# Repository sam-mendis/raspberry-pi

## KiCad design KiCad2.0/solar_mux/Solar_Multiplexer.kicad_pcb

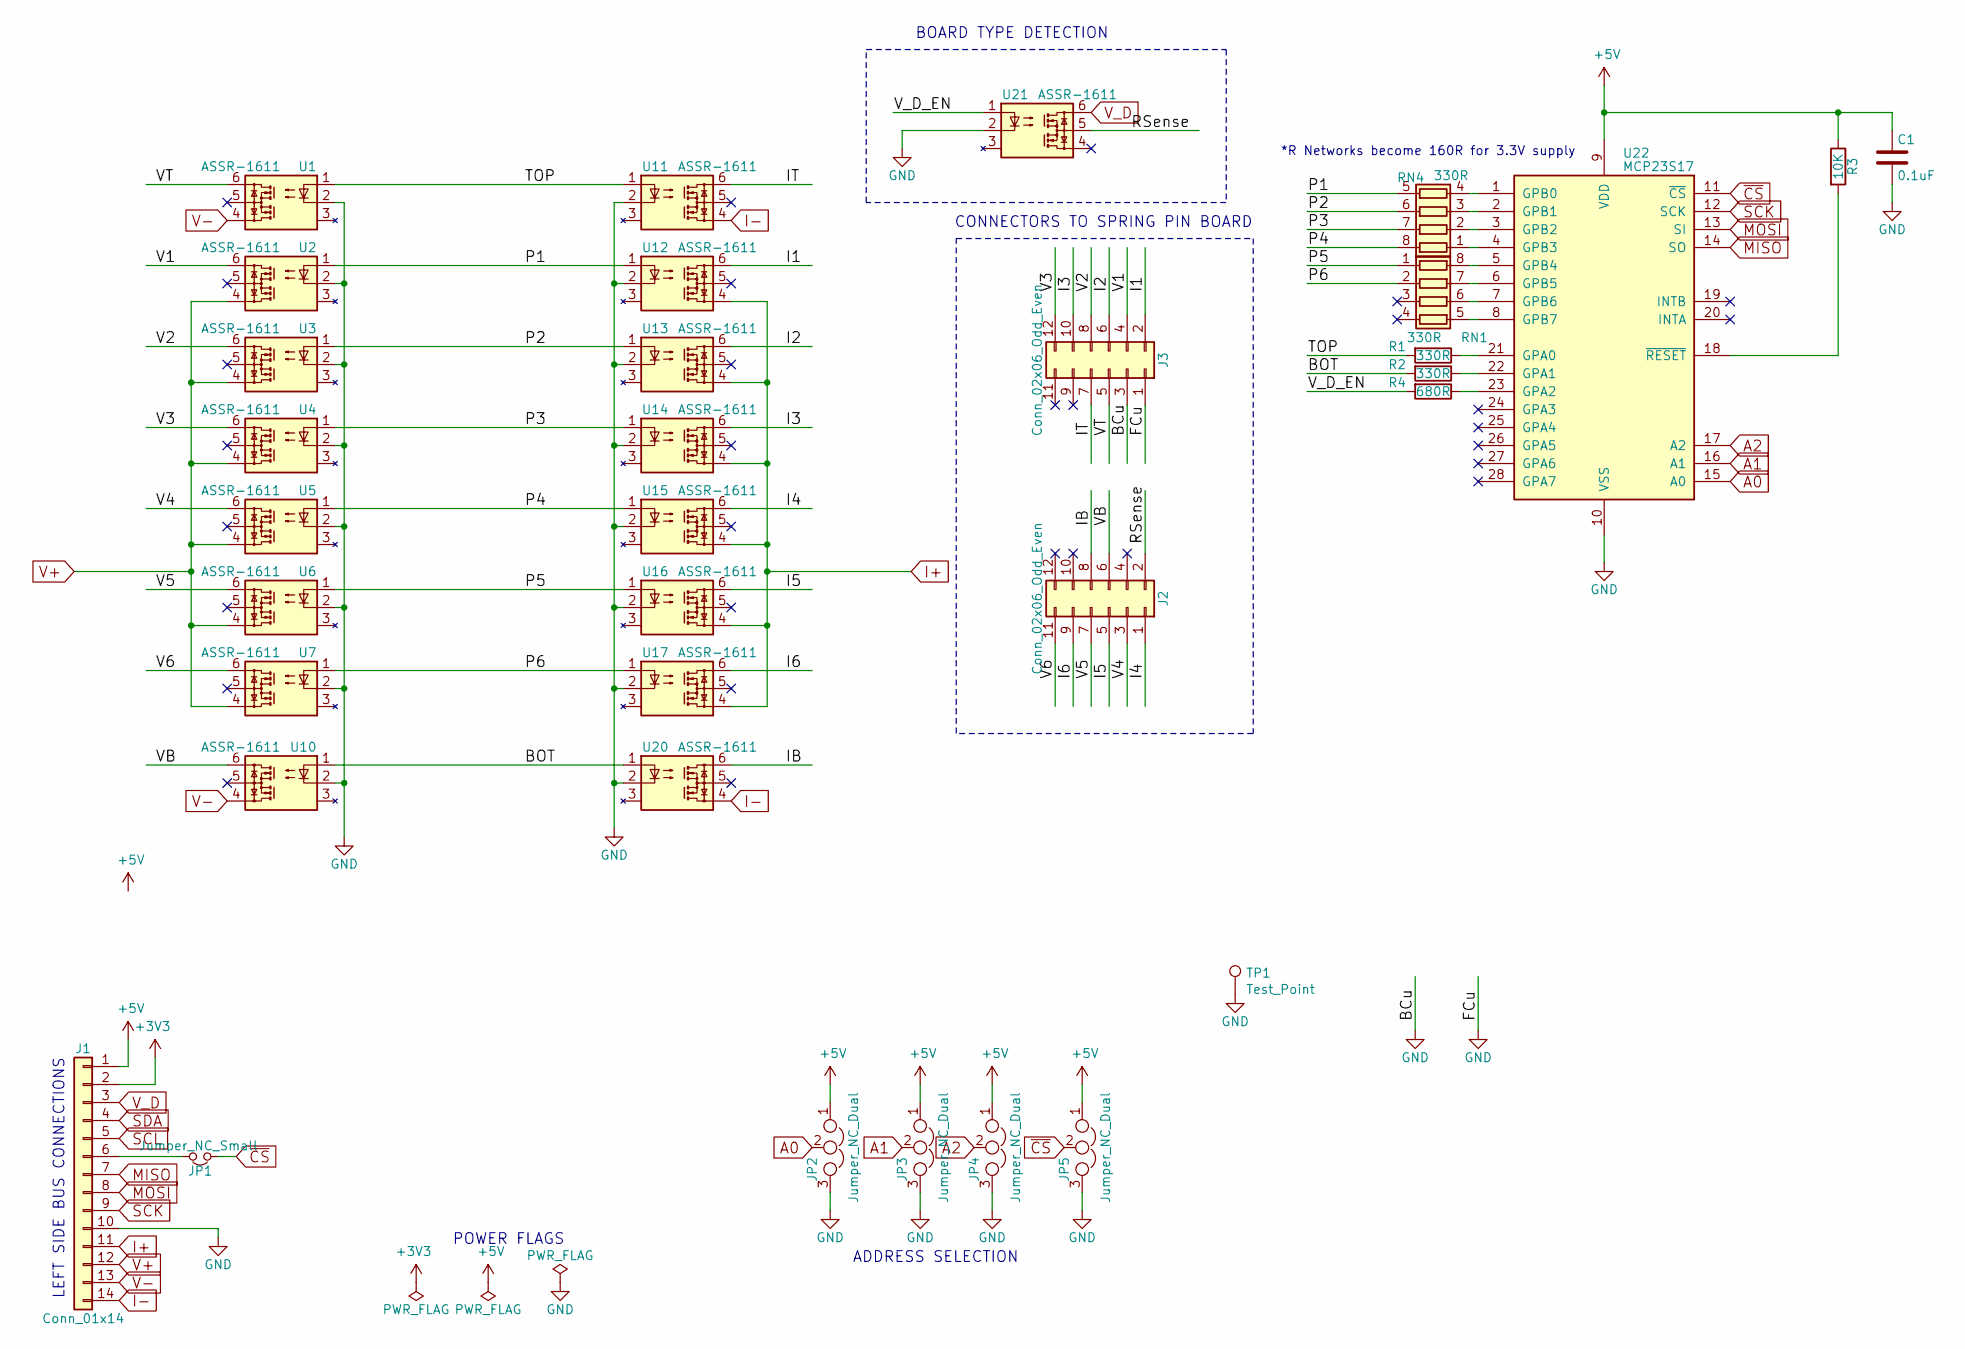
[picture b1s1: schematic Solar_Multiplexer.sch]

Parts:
C1: 0.1uF; CP_Radial_D8.0mm_P2.50mm; farnellCode 1759312
J1: Conn_01x14; PinHeader_1x14_P2.54mm_Vertical; farnellCode 2037821
J2: Conn_02x06_Odd_Even; PinHeader_2x06_P2.54mm_Vertical
J3: Conn_02x06_Odd_Even; PinHeader_2x06_P2.54mm_Vertical; FarnellPart 1930232
JP1: Jumper_NC_Small; SolderJumper-2_P1.3mm_Open_RoundedPad1.0x1.5mm
JP2, JP3, JP4, JP5: Jumper_NC_Dual; SolderJumper-3_P1.3mm_Open_RoundedPad1.0x1.5mm_NumberLabels
R1, R2: 330R; R_Axial_DIN0309_L9.0mm_D3.2mm_P15.24mm_Horizontal; farnellCode 2073607
R3: 10K; R_Axial_DIN0309_L9.0mm_D3.2mm_P15.24mm_Horizontal; farnellCode 2826357
R4: 680R; R_Axial_DIN0309_L9.0mm_D3.2mm_P15.24mm_Horizontal; farnellCode 2694489
RN1, RN4: 330R; R_Array_Convex_4x1206; digikey 744C083331JPCT-ND
TP1: Test_Point; TestPoint_Pad_2.5x2.5mm; farnell code 2293786
U1, U2, U3, U4, U5, U6, U7, U10, U11, U12, U13, U14, U15, U16, U17, U20, U21: ASSR-1611; DIP-6_W7.62mm; farnellCode 1708441
U22: MCP23S17; DIP-28_W7.62mm; farnellCode 1292238

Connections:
+3V3: J1.2
+5V: C1.1, J1.1, JP2.1, JP3.1, JP4.1, JP5.1, R3.1, U22.9 (VDD)
/BOT: R2.2, U10.1, U20.1
/I1: J3.2, U12.6
/I2: J3.6, U13.6
/I3: J3.10, U14.6
/I4: J2.1, U15.6
/I5: J2.5, U16.6
/I6: J2.9, U17.6
/IB: J2.8, U20.6
/IT: J3.7, U11.6
/P1: RN4.5 (R4.2), U2.1, U12.1
/P2: RN4.6 (R3.2), U3.1, U13.1
/P3: RN4.7 (R2.2), U4.1, U14.1
/P4: RN4.8 (R1.2), U5.1, U15.1
/P5: RN1.1 (R1.1), U6.1, U16.1
/P6: RN1.2 (R2.1), U7.1, U17.1
/RSense: J2.2, U21.5
/TOP: R1.2, U1.1, U11.1
/V1: J3.4, U2.6
/V2: J3.8, U3.6
/V3: J3.12, U4.6
/V4: J2.3, U5.6
/V5: J2.7, U6.6
/V6: J2.11, U7.6
/VB: J2.6, U10.6
/VT: J3.5, U1.6
/V_D_EN: R4.2, U21.1
A0: JP2.2, U22.15 (A0)
A1: JP3.2, U22.16 (A1)
A2: JP4.2, U22.17 (A2)
GND: C1.2, J1.10, J3.1, J3.3, JP2.3, JP3.3, JP4.3, JP5.3, TP1.1, U1.2, U2.2, U3.2, U4.2, U5.2, U6.2, U7.2, U10.2, U11.2, U12.2, U13.2, U14.2, U15.2, U16.2, U17.2, U20.2, U21.2, U22.10 (VSS)
I+: J1.11, U12.4, U13.4, U14.4, U15.4, U16.4, U17.4
I-: J1.14, U11.4, U20.4
MISO: J1.7, U22.14 (SO)
MOSI: J1.8, U22.13 (SI)
unnamed: J1.6, JP1.2
unnamed: R1.1, U22.21 (GPA0)
unnamed: R2.1, U22.22 (GPA1)
unnamed: R3.2, U22.18 (~RESET~)
unnamed: R4.1, U22.23 (GPA2)
unnamed: RN1.5 (R4.2), U22.8 (GPB7)
unnamed: RN1.6 (R3.2), U22.7 (GPB6)
unnamed: RN1.7 (R2.2), U22.6 (GPB5)
unnamed: RN1.8 (R1.2), U22.5 (GPB4)
unnamed: RN4.1 (R1.1), U22.4 (GPB3)
unnamed: RN4.2 (R2.1), U22.3 (GPB2)
unnamed: RN4.3 (R3.1), U22.2 (GPB1)
unnamed: RN4.4 (R4.1), U22.1 (GPB0)
SCK: J1.9, U22.12 (SCK)
SCL: J1.5
SDA: J1.4
V+: J1.12, U2.4, U3.4, U4.4, U5.4, U6.4, U7.4
V-: J1.13, U1.4, U10.4
V_D: J1.3, U21.6
~CS: JP1.1, JP5.2, U22.11 (~CS~)

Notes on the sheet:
ADDRESS SELECTION
POWER FLAGS
BOARD TYPE DETECTION
CONNECTORS TO SPRING PIN BOARD
LEFT SIDE BUS CONNECTIONS
*R Networks become 160R for 3.3V supply

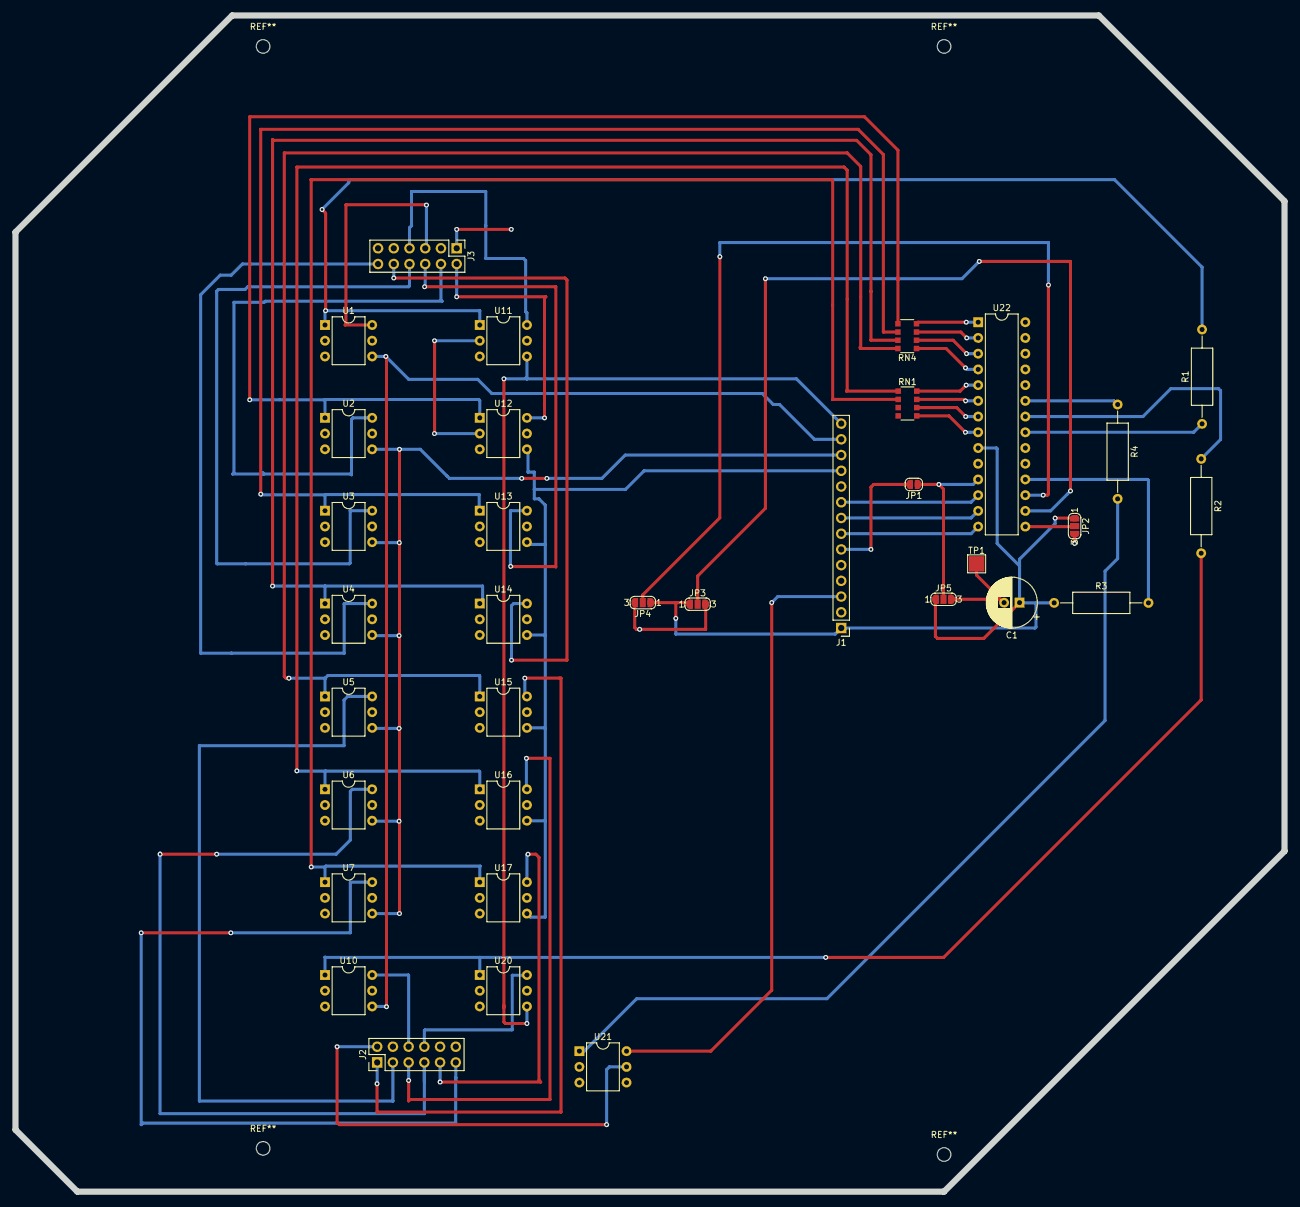
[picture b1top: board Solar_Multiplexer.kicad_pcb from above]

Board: 2 copper layers, 205.0 x 190.0 mm, 34 parts (0 on the bottom side), 53 nets.

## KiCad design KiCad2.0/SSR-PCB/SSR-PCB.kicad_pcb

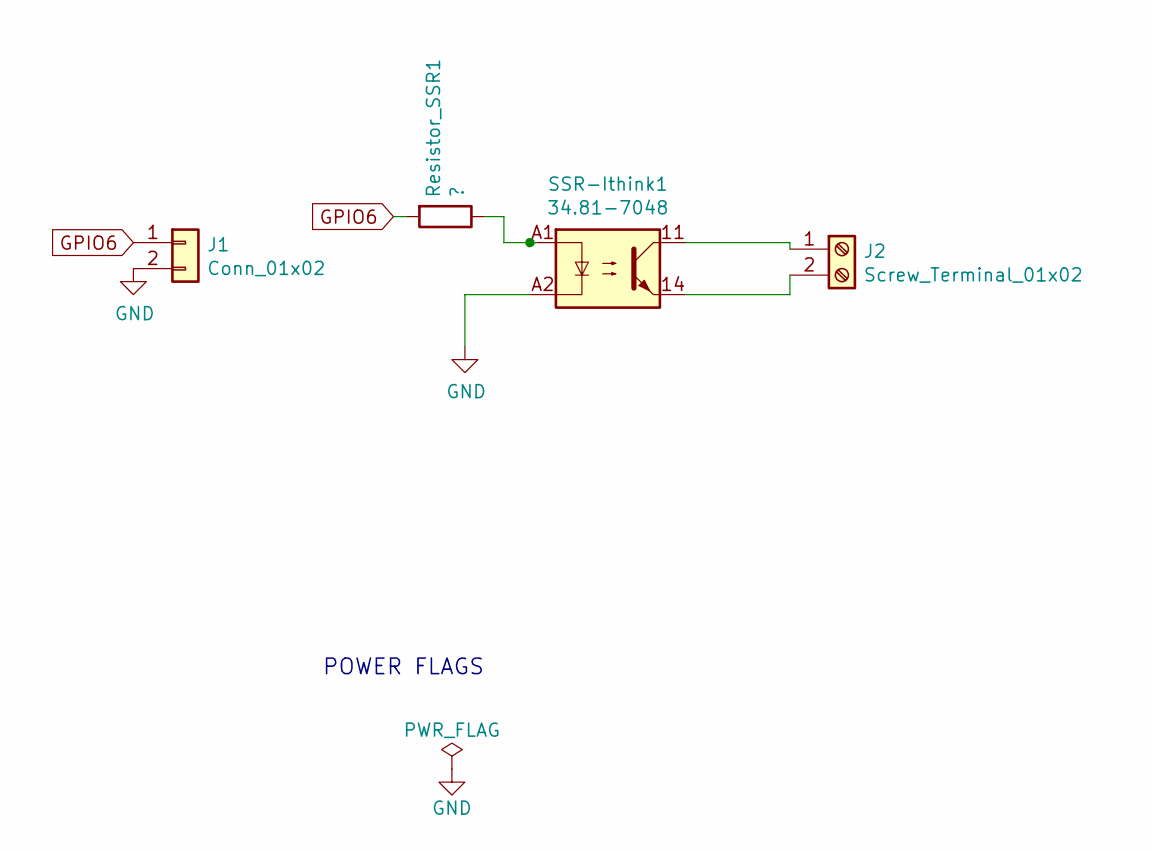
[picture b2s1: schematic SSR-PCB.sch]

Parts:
J1: Conn_01x02; PinHeader_1x02_P2.54mm_Vertical
J2: Screw_Terminal_01x02; TerminalBlock_Phoenix_MKDS-1,5-2_1x02_P5.00mm_Horizontal
Resistor_SSR1: ?; R_Axial_DIN0516_L15.5mm_D5.0mm_P20.32mm_Horizontal
SSR-Ithink1: 34.81-7048; Finder_34.81

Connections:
GND: J1.2, SSR-Ithink1.A2
GPIO6: J1.1, Resistor_SSR1.2
unnamed: J2.1, SSR-Ithink1.11
unnamed: J2.2, SSR-Ithink1.14
unnamed: Resistor_SSR1.1, SSR-Ithink1.A1

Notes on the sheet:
POWER FLAGS

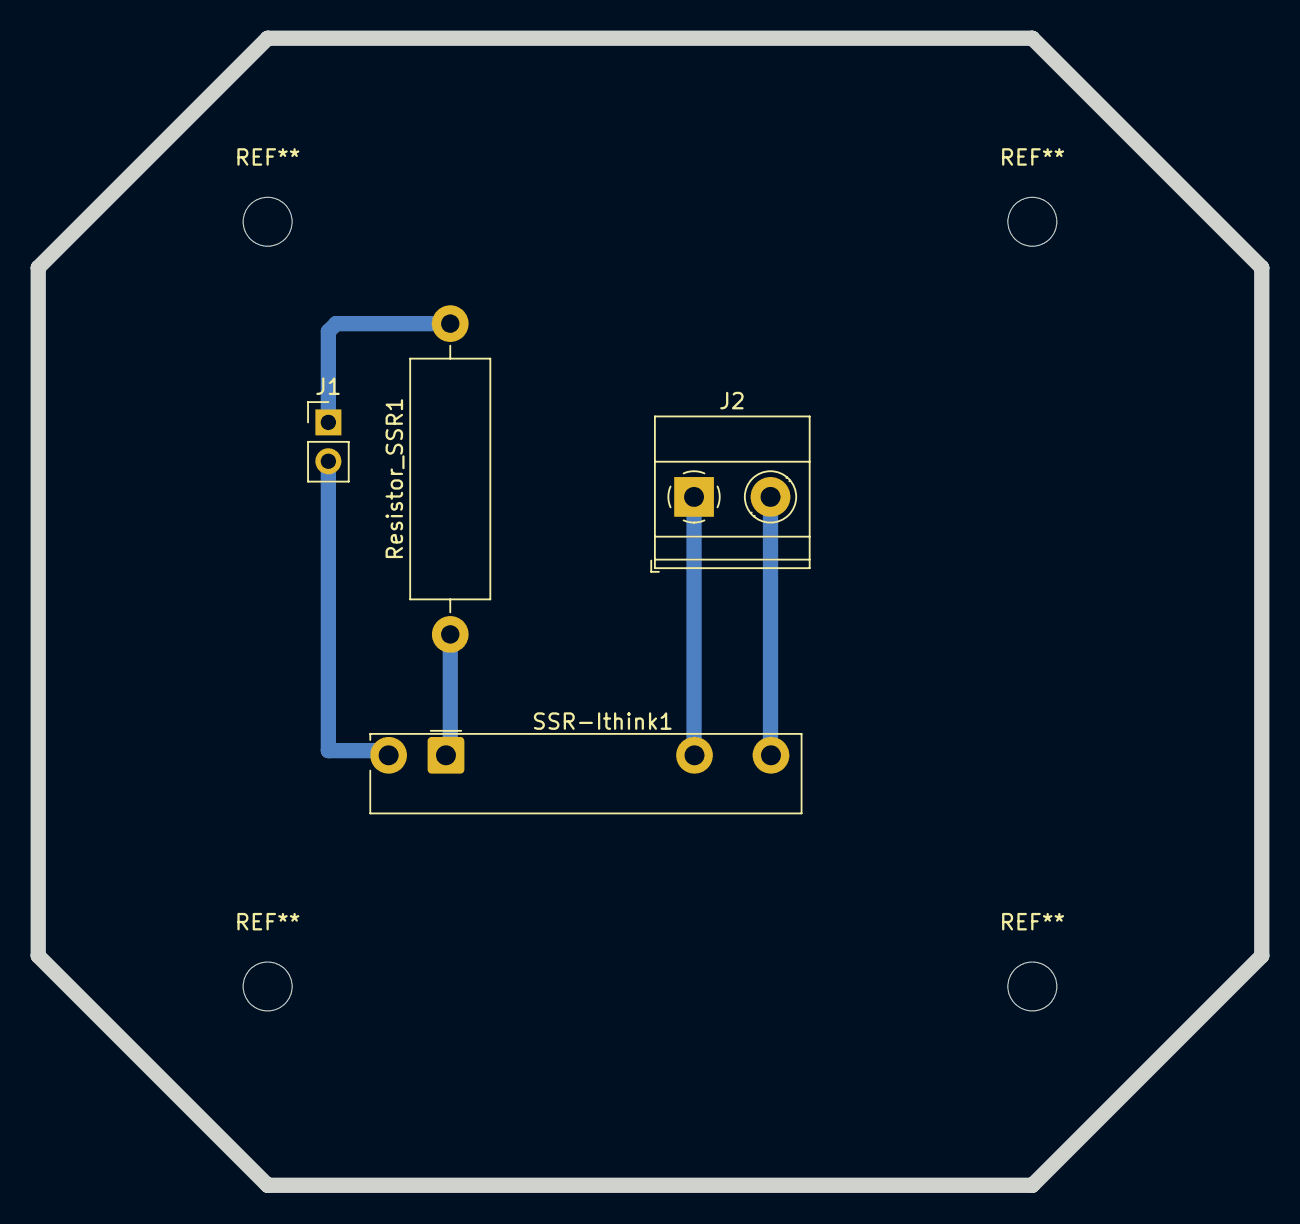
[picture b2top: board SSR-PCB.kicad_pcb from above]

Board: 4 copper layers, 80.0 x 75.0 mm, 4 parts (0 on the bottom side), 5 nets.

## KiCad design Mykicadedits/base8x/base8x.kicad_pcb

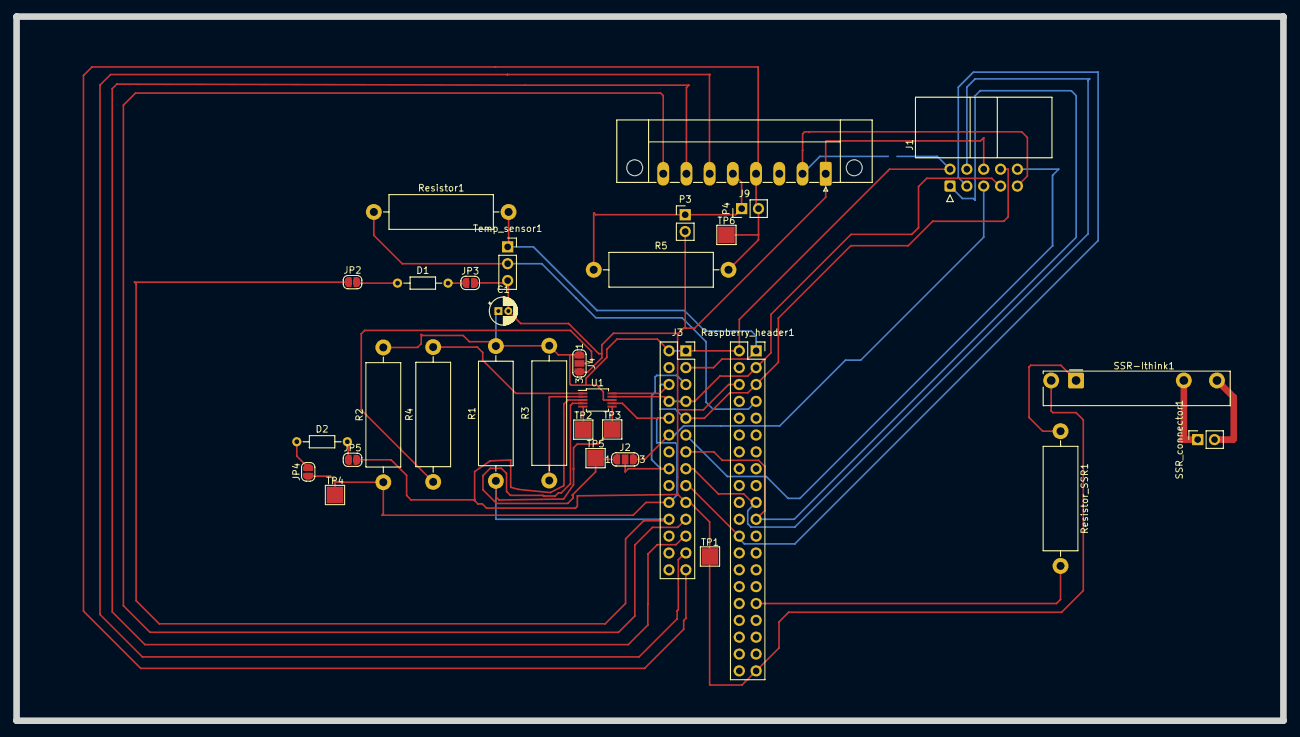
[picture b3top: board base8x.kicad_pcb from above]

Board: 4 copper layers, 191.0 x 106.2 mm, 33 parts (1 on the bottom side), 33 nets.

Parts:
C1: 1uF; CP_Radial_D4.0mm_P1.50mm
D1, D2: BPW21; R_Axial_DIN0204_L3.6mm_D1.6mm_P7.62mm_Horizontal
J1: Conn_02x05_Odd_Even; IDC-Header_2x05_P2.54mm_Horizontal
J2, J4: GS3; SolderJumper-3_P1.3mm_Open_RoundedPad1.0x1.5mm_NumberLabels
J3: Conn_02x14_Counter_Clockwise; PinSocket_2x14_P2.54mm_Vertical
J9: Screw_Terminal_01x08; PhoenixContact_MC_1,5_8-GF-3.5_1x08_P3.50mm_Horizontal_Thre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
JP2, JP3, JP4, JP5, JP6: Jumper_NO_Small; SolderJumper-2_P1.3mm_Open_RoundedPad1.0x1.5mm
P3, P4: CONN_01X02; PinHeader_1x02_P2.54mm_Vertical
R1, R2: 1.2K; R_Axial_DIN0516_L15.5mm_D5.0mm_P20.32mm_Horizontal
R3, R4: 10K; R_Axial_DIN0516_L15.5mm_D5.0mm_P20.32mm_Horizontal
R5: 1; R_Axial_DIN0516_L15.5mm_D5.0mm_P20.32mm_Horizontal
Raspberry_header1: Conn_02x20_Odd_Even; PinSocket_2x20_P2.54mm_Vertical
Resistor1: 4.7k; R_Axial_DIN0516_L15.5mm_D5.0mm_P20.32mm_Horizontal
Resistor_SSR1: ?; R_Axial_DIN0516_L15.5mm_D5.0mm_P20.32mm_Horizontal
SSR-Ithink1: 34.81-7048; Finder_34.81
SSR_connector1: Conn_01x02_Female; PinSocket_1x02_P2.54mm_Vertical
TP1, TP2, TP3, TP4, TP5, TP6: Test_Point; TestPoint_Pad_2.5x2.5mm
Temp_sensor1: Conn_01x03_Female; PinSocket_1x03_P2.54mm_Vertical
U1: ADS1115; MSOP-10_3x3mm_P0.5mm

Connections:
+3V3: J3.3, Raspberry_header1.1, Resistor1.2, Temp_sensor1.1
+5V: C1.1, J1.2, J3.1, J3.2, J4.1, JP6.1, R1.2, R2.2, R3.2, Raspberry_header1.2, U1.8
/Vin: J1.9, J9.2, JP6.2
A_I+: J3.21, J9.8
A_I-: J3.27, J9.4, P4.2, R5.2, TP6.1
A_I-_EXT: J9.5, P3.1, P4.1, R5.1
A_V+: J3.23, J9.7
A_V-: J3.25, J9.6
A_V_D: J2.2, J3.5, J3.16
A_V_D_EXT: J1.5, J2.3, J3.12
A_V_D_LOC: J2.1, TP5.1, U1.4
CLK0: Raspberry_header1.7, Resistor1.1, Temp_sensor1.2
GND: C1.2, J1.6, J3.19, J4.3, J9.1, JP3.2, JP5.2, P3.2, Raspberry_header1.6, Raspberry_header1.39, SSR-Ithink1.A2, TP1.1, Temp_sensor1.3, U1.3
GPIO6: Raspberry_header1.31, Resistor_SSR1.2
HELP1: J3.22, JP2.1, R1.1, TP3.1, U1.6
HELP3: J3.10, J3.20, JP4.1, R2.1, TP4.1, U1.7
MISO: J1.1, J3.13, Raspberry_header1.21
MOSI: J1.4, J3.15, Raspberry_header1.19
unnamed: D1.1, JP2.2
unnamed: D1.2, JP3.1
unnamed: D2.1, JP4.2
unnamed: D2.2, JP5.1
unnamed: J4.2, R4.1
unnamed: R3.1, U1.2
unnamed: R4.2, U1.1
unnamed: Resistor_SSR1.1, SSR-Ithink1.A1
unnamed: SSR-Ithink1.11, SSR_connector1.1
unnamed: SSR-Ithink1.14, SSR_connector1.2
unnamed: TP2.1, U1.5
SCK: J1.3, J3.17, Raspberry_header1.24
SCL: J1.8, J3.6, J3.9, Raspberry_header1.5, U1.10
SDA: J1.7, J3.7, J3.8, Raspberry_header1.3, U1.9
~A_CS: J1.10, J3.11

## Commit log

2020-12-22 copying from other respository
2020-12-28 COMMENT
2021-01-13 Sam Edit
2021-01-20 edits
2021-01-21 2 functions simultaneously
2021-01-31 Creating Venv and new gui file to tidy up code
2021-02-02 editing controller further
2021-02-09 edits on 09/02
2021-02-10 Big Edits
2021-02-10 not that big changes
2021-02-11 Creating Copies of kicad for me to edit
2021-02-12 Greys Updated code
2021-02-12 it was fucked
2021-02-12 Leave it!
2021-02-14 Big Changes
2021-02-14 Finishing Touches
2021-02-15 changes?
2021-02-21 major rebuild
2021-02-22 Final Edits
2021-02-24 Clean Up
2021-02-24 Important Changes
2021-03-08 Good edits
2021-03-13 writing code for calcium test
2021-05-04 important
